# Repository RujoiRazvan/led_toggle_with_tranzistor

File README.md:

# Led toggle by button using a transistor
## My first project with a transistor

If the button is pressed, the green light is turned on and in rest of time, the red led is turned on and the green led is off.
Simulation made in Proteus 8 and the PCB Design is made in KiCad

Components:
* PushButton
* Green and Orange Led - 5mm
* 2x 1kOhm Resistor
* 1x 10kOhm Resistor
* BC337 - NPN Transistor
* PCB Connector
* 9V Battery

Circuit

Ledul verde - activ

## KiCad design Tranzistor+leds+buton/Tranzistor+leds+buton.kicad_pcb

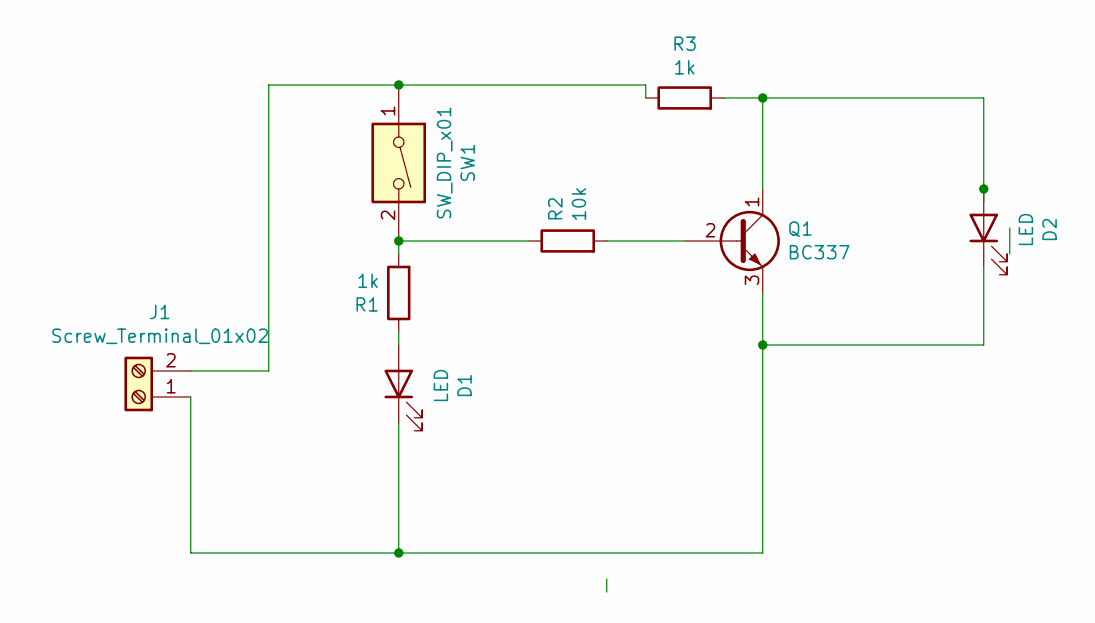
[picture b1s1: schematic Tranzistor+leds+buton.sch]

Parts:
D1, D2: LED; LED_D5.0mm
J1: Screw_Terminal_01x02; TerminalBlock_Phoenix_MKDS-1,5-2_1x02_P5.00mm_Horizontal
Q1: BC337; TO-92_Inline
R1, R3: 1k; R_Axial_DIN0204_L3.6mm_D1.6mm_P2.54mm_Vertical
R2: 10k; R_Axial_DIN0204_L3.6mm_D1.6mm_P2.54mm_Vertical
SW1: SW_DIP_x01; SW_PUSH_6mm_H5mm

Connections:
unnamed: D1.1 (K), D2.1 (K), J1.1, Q1.3 (E)
unnamed: D1.2 (A), R1.1
unnamed: D2.2 (A), Q1.1 (C), R3.2
unnamed: J1.2, R3.1, SW1.1
unnamed: Q1.2 (B), R2.2
unnamed: R1.2, R2.1, SW1.2

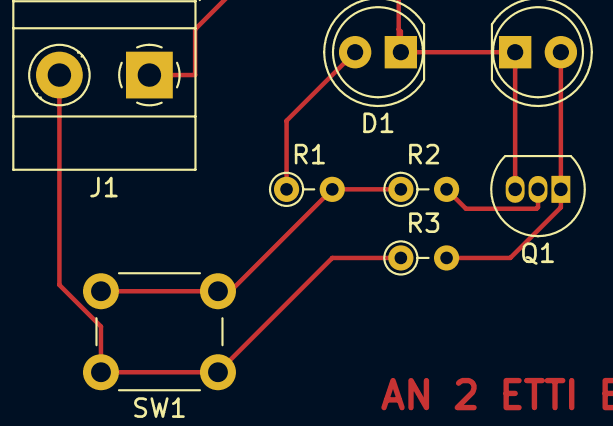
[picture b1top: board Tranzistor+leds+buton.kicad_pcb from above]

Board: 2 copper layers, 8 parts (0 on the bottom side), 6 nets.
